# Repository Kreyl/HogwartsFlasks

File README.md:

# HogwartsFlasks
Hogwarts Flasks is a project for realictic models of Hogwarts hourglasses for LARPs and events
You may look at them here https://ostranna.ru/hogwartsflasks (text is at Russian, but photoes are international)

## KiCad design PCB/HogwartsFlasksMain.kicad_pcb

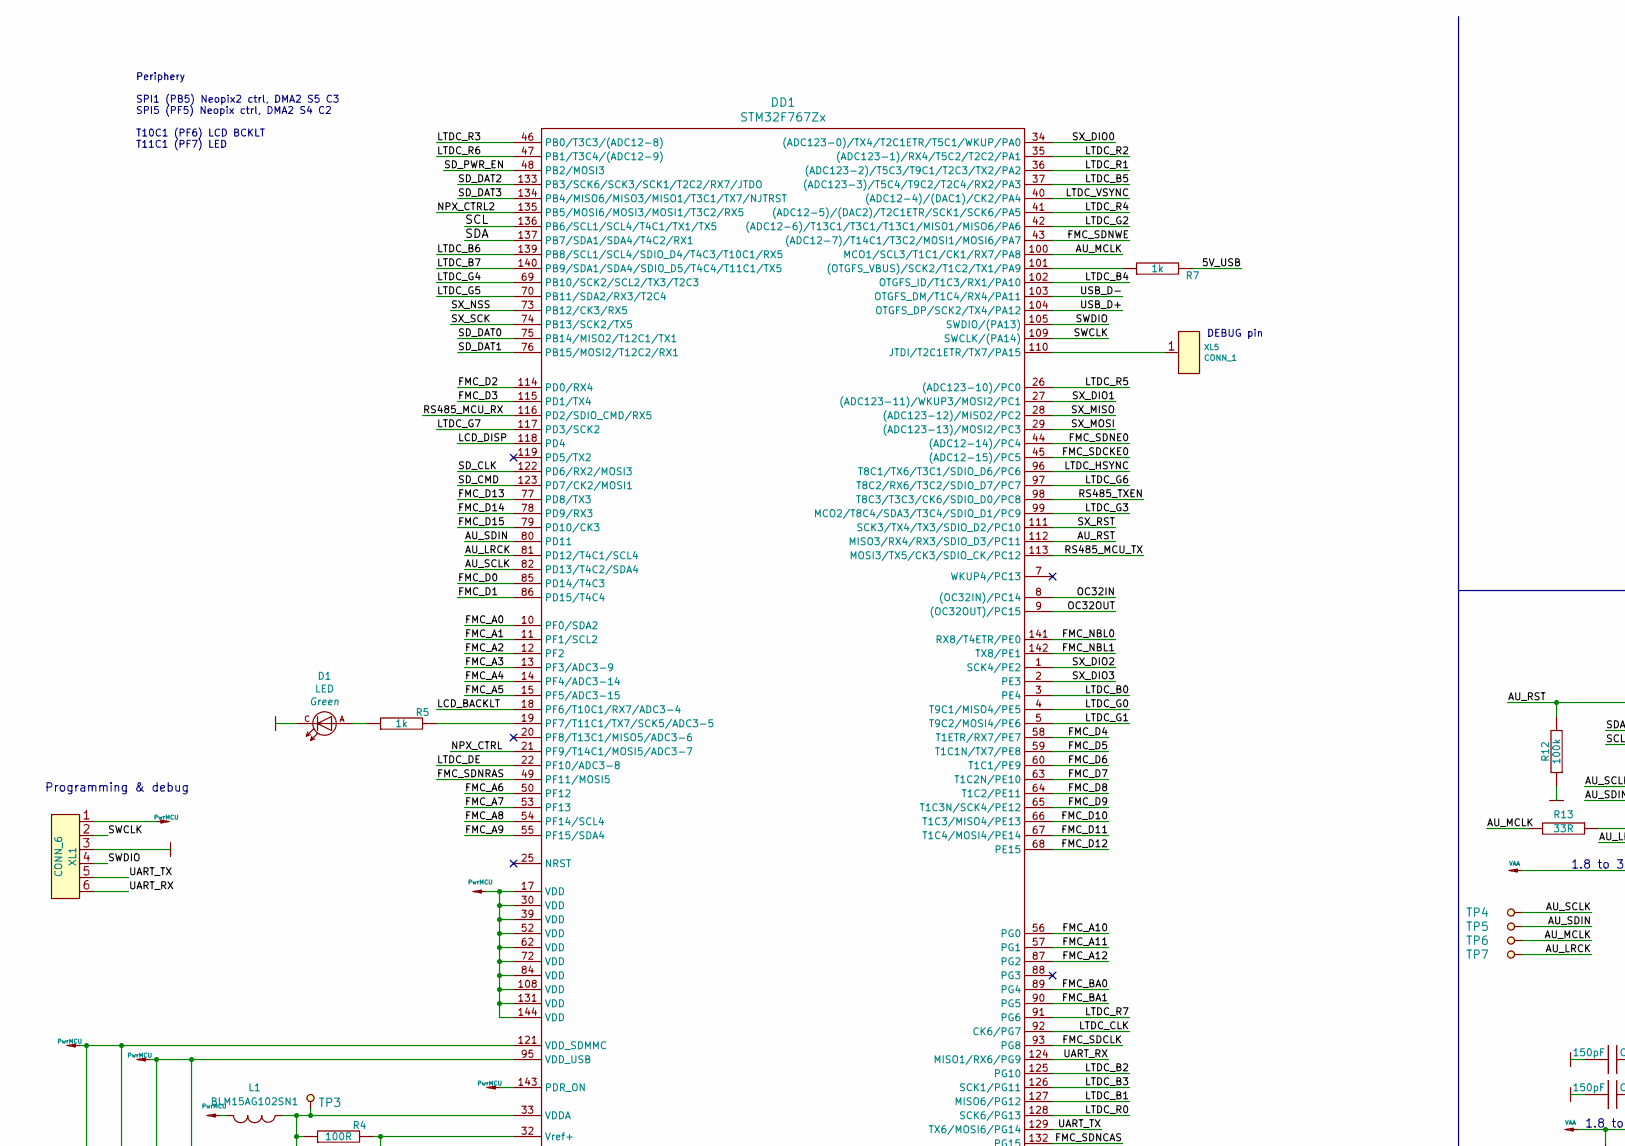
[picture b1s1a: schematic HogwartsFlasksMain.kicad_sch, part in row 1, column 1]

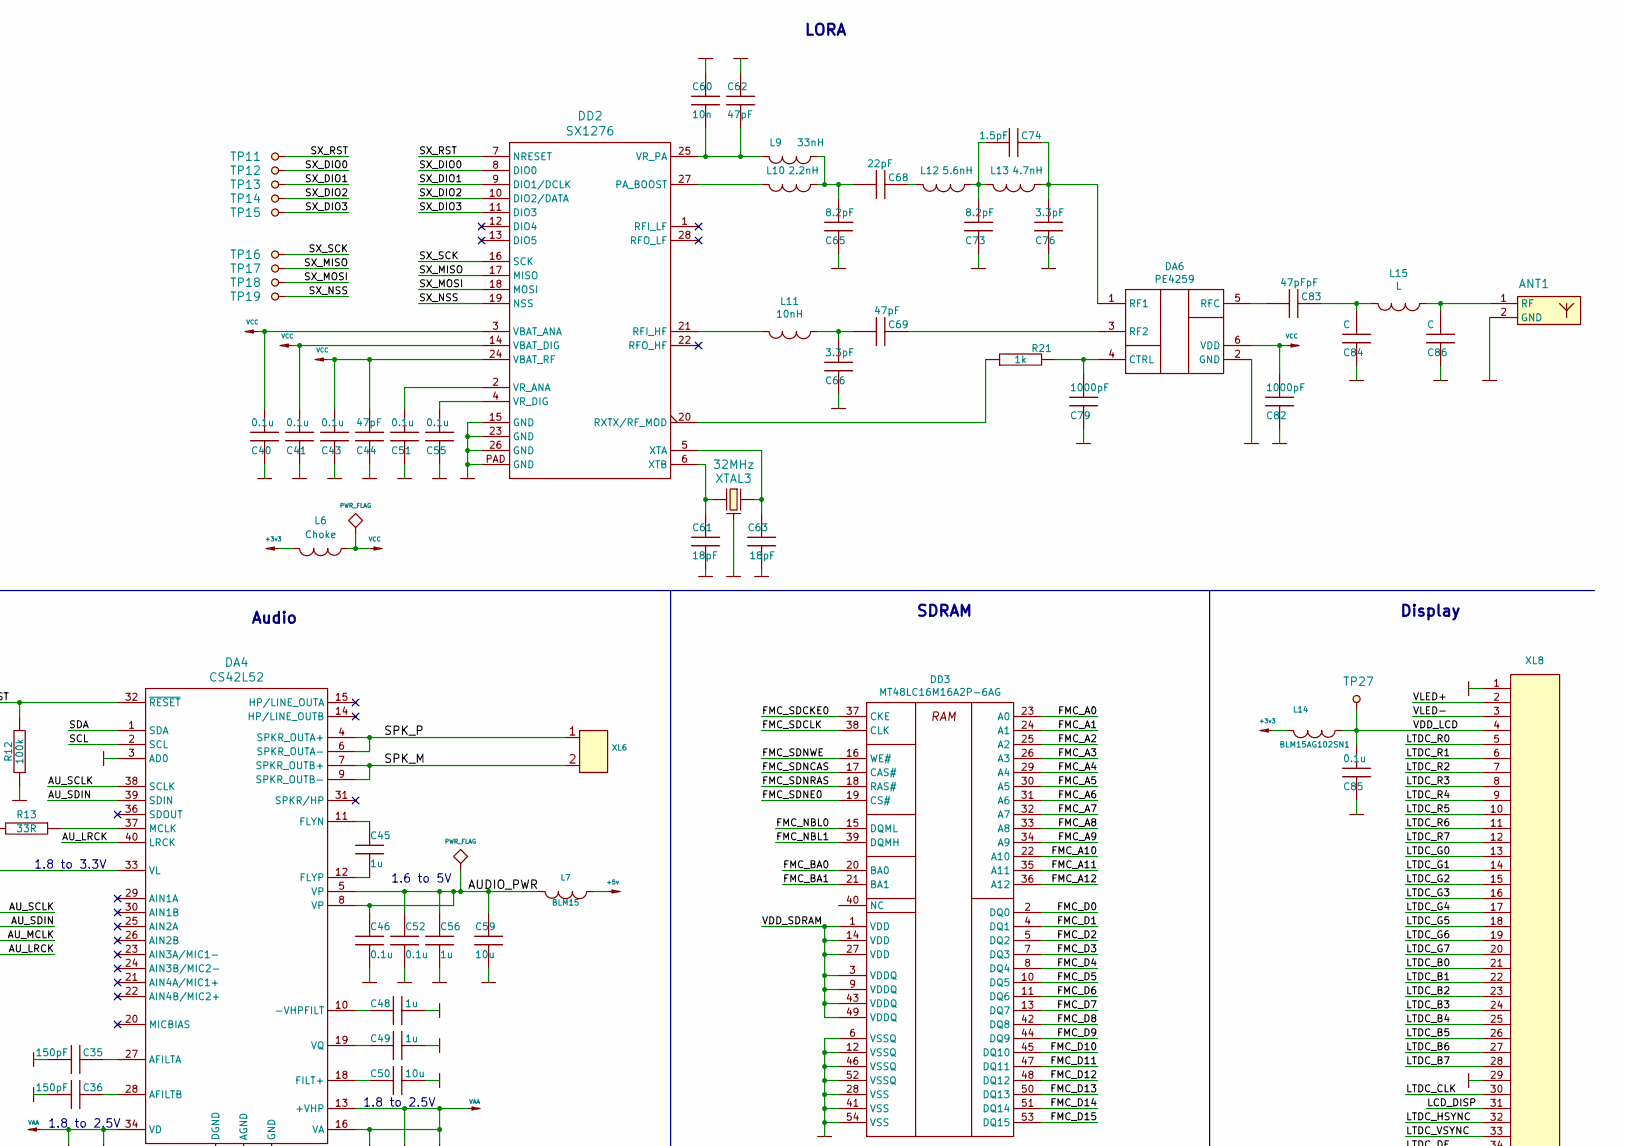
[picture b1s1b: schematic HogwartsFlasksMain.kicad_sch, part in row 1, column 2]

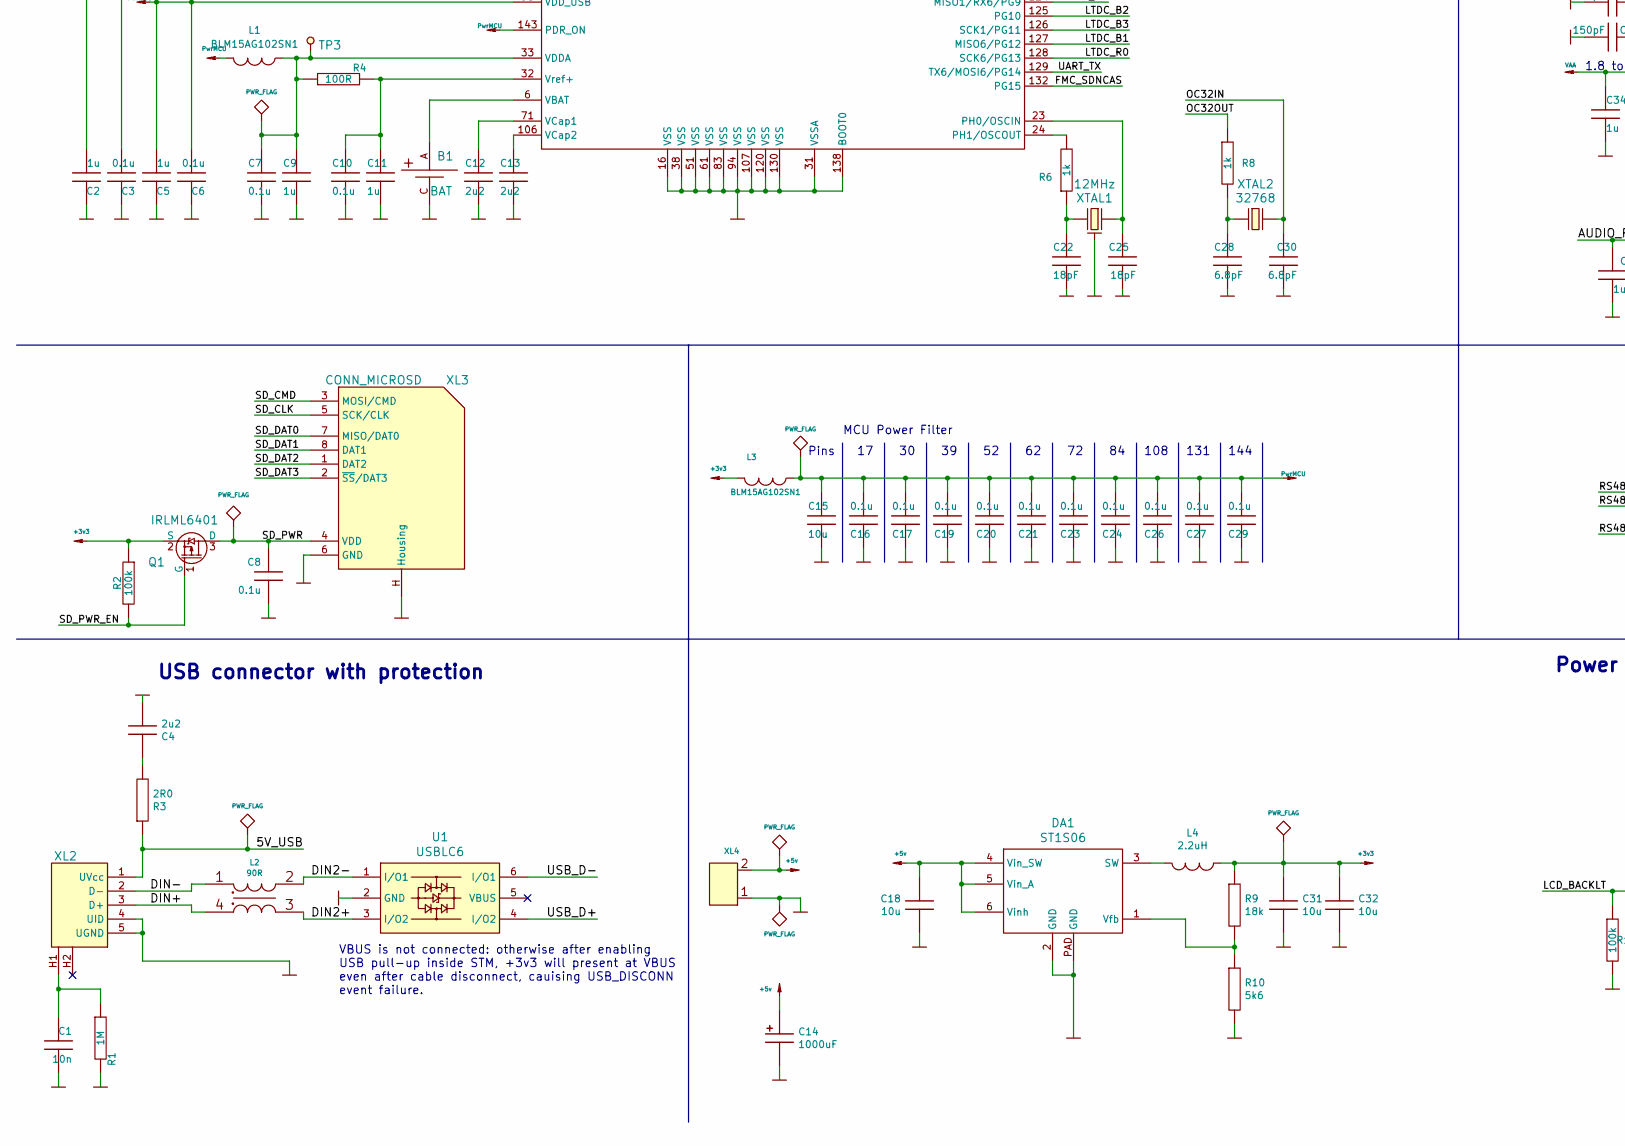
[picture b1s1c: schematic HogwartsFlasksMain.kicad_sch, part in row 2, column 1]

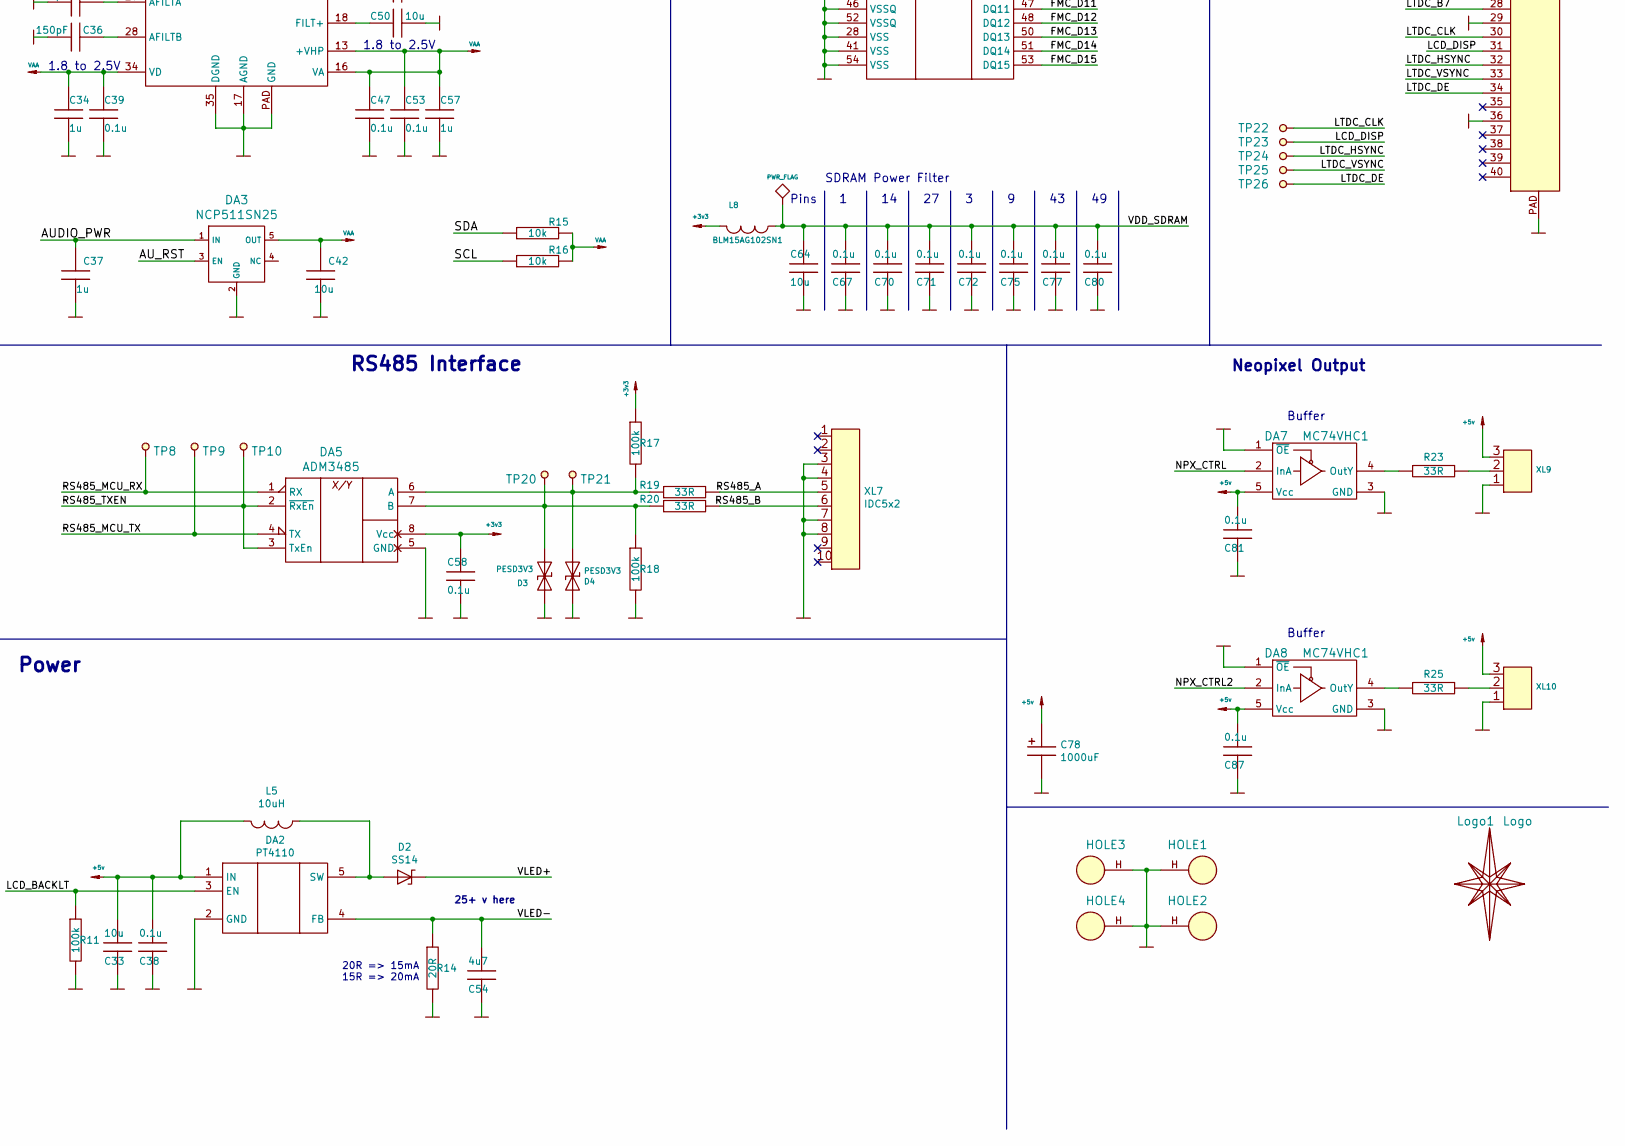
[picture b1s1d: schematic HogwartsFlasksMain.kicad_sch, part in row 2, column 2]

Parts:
ANT1: ANT_GENERAL; ANT_868_IFA_SIMPLEJOY
B1: BAT; BATTERY_CH7410
C1: 10n; CAP_0603_Silks
C2, C5, C9, C11, C34, C37, C45, C48, C49, C56, C57: 1u; CAP_0603_Silks
C3, C6, C7, C8, C10, C16, C17, C19, C20, C21, C23, C24, C26, C27, C29, C38, C39, C46, C47, C52, C53, C58, C67, C70, C71, C72, C75, C77, C80, C81, C85, C87: 0.1u; CAP_0603_Silks
C4, C12, C13: 2u2; CAP_0603_Silks
C14, C78: 1000uF; CAP_10xxR
C15, C18, C31, C32, C33, C42, C50, C59, C64: 10u; CAP_0603_Silks
C22, C25, C61, C63: 18pF; CAP_0603_Silks
C28, C30: 6.8pF; CAP_0603_Silks
C35, C36: 150pF; CAP_0603_Silks
C40, C41, C43, C51, C55: 0.1u; CAP_0402
C44, C62, C69: 47pF; CAP_0402
C54: 4u7; CAP_0805
C60: 10n; CAP_0402
C65, C73: 8.2pF; CAP_0402
C66, C76: 3.3pF; CAP_0402
C68: 22pF; CAP_0402
C74: 1.5pF; CAP_0402
C79, C82: 1000pF; CAP_0402
C83: 47pFpF; CAP_0402
C84, C86: C; CAP_0402
D1: LED; LED_0603
D2: SS14; SMA_DO214AC
D3, D4: PESD3V3; SOD323
DA1: ST1S06; DFN6_3x3
DA2: PT4110; SOT89-5
DA3: NCP511SN25; SOT23-5
DA4: CS42L52; QFN40
DA5: ADM3485; SO8_150MIL
DA6: PE4259; SC70
DA7, DA8: MC74VHC1; SOT23-5
DD1: STM32F767Zx; QFP-144_20x20_Pitch0.5mm
DD2: SX1276; QFN-28_EP_6x6_Pitch0.65mm
DD3: MT48LC16M16A2P-6AG; TSSOP54_400MIL_P08
HOLE1, HOLE2, HOLE3, HOLE4: HOLE_METALLED; Hole3_5_out6mm
L1, L3, L8, L14: BLM15AG102SN1; IND_0402
L2: 90R; DLW21SN
L4: 2.2uH; IND_SRN2512
L5: 10uH; IND_SRN3015
L6: Choke; IND_0402
L7: BLM15; IND_0402
L9: 33nH; IND_0402
L10: 2.2nH; IND_0402
L11: 10nH; IND_0402
L12: 5.6nH; IND_0402
L13: 4.7nH; IND_0402
L15: L; IND_0402
Logo1: Logo; Ostranna_12d7_10d1
Q1: IRLML6401; SOT23-3
R1: 1M; RES_0603
R2, R11, R12, R17, R18: 100k; RES_0603
R3: 2R0; RES_0603
R4: 100R; RES_0603
R5, R6, R7, R8, R21: 1k; RES_0603
R9: 18k; RES_0603
R10: 5k6; RES_0603
R13, R19, R20, R23, R25: 33R; RES_0603
R14: 20R; RES_0603
R15, R16: 10k; RES_0603
TP3, TP4, TP5, TP6, TP7, TP8, TP9, TP10, TP11, TP12, TP13, TP14, TP15, TP16, TP17, TP18, TP19, TP20, TP21, TP22, TP23, TP24, TP25, TP26, TP27: TESTPOINT; TESTPOINT_1MM
U1: USBLC6; SOT23-6
XL1: CONN_6; PLS-6_LOCK
XL2: USB_MICRO_2H; USBmicro_MOLEX_1050170001
XL3: CONN_MICROSD; MICROSD_CAP_FIX05A
XL4: CONN_2; TermiBlockHeader_508_x2_R
XL5: CONN_1; PLS-1Rnd
XL6: CONN_2; W02_Pitch_2d54
XL7: IDC5x2; IDC-Header_2x5_P2.54mm_Vertical
XL8: CONN_40; FFC_0d5x40_flip
XL9, XL10: CONN_3; SLD_3_2D5
XTAL1: 12MHz; 03225C4
XTAL2: 32768; 03215C2
XTAL3: 32MHz; 03225C4

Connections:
+3v3: C31.1, C32.1, C58.2, DA5.8 (Vcc), L3.2, L4.2, L6.2, L8.2, L14.2, Q1.2 (S), R2.1, R9.1, R17.1
+5v: C14.1, C18.1, C33.1, C38.1, C78.1, C81.1, C87.1, DA1.4 (Vin_SW), DA1.5 (Vin_A), DA1.6 (Vinh), DA2.1 (IN), DA7.5 (Vcc), DA8.5 (Vcc), L5.1, L7.2, XL4.2 (PM), XL9.3, XL10.3
/5V_USB: R3.1, R7.2, XL2.1 (UVcc)
/AUDIO_PWR: C37.1, C46.1, C52.1, C56.1, C59.2, DA3.1 (IN), DA4.5 (VP), DA4.8 (VP), L7.1
/AU_LRCK: DA4.40 (LRCK), DD1.81 (PD12/T4C1/SCL4), TP7.1
/AU_MCLK: DD1.100 (MCO1/SCL3/T1C1/CK1/RX7/PA8), R13.2, TP6.1
/AU_RST: DA3.3 (EN), DA4.32 (~RESET), DD1.112 (MISO3/RX4/RX3/SDIO_D3/PC11), R12.2
/AU_SCLK: DA4.38 (SCLK), DD1.82 (PD13/T4C2/SDA4), TP4.1
/AU_SDIN: DA4.39 (SDIN), DD1.80 (PD11), TP5.1
/DIN2+: L2.3, U1.3 (I/O2)
/DIN2-: L2.2, U1.1 (I/O1)
/DIN+: L2.4, XL2.3 (D+)
/DIN-: L2.1, XL2.2 (D-)
/FMC_A0: DD1.10 (PF0/SDA2), DD3.23 (A0)
/FMC_A1: DD1.11 (PF1/SCL2), DD3.24 (A1)
/FMC_A2: DD1.12 (PF2), DD3.25 (A2)
/FMC_A3: DD1.13 (PF3/ADC3-9), DD3.26 (A3)
/FMC_A4: DD1.14 (PF4/ADC3-14), DD3.29 (A4)
/FMC_A5: DD1.15 (PF5/ADC3-15), DD3.30 (A5)
/FMC_A6: DD1.50 (PF12), DD3.31 (A6)
/FMC_A7: DD1.53 (PF13), DD3.32 (A7)
/FMC_A8: DD1.54 (PF14/SCL4), DD3.33 (A8)
/FMC_A9: DD1.55 (PF15/SDA4), DD3.34 (A9)
/FMC_A10: DD1.56 (PG0), DD3.22 (A10)
/FMC_A11: DD1.57 (PG1), DD3.35 (A11)
/FMC_A12: DD1.87 (PG2), DD3.36 (A12)
/FMC_BA0: DD1.89 (PG4), DD3.20 (BA0)
/FMC_BA1: DD1.90 (PG5), DD3.21 (BA1)
/FMC_D0: DD1.85 (PD14/T4C3), DD3.2 (DQ0)
/FMC_D1: DD1.86 (PD15/T4C4), DD3.4 (DQ1)
/FMC_D2: DD1.114 (PD0/RX4), DD3.5 (DQ2)
/FMC_D3: DD1.115 (PD1/TX4), DD3.7 (DQ3)
/FMC_D4: DD1.58 (T1ETR/RX7/PE7), DD3.8 (DQ4)
/FMC_D5: DD1.59 (T1C1N/TX7/PE8), DD3.10 (DQ5)
/FMC_D6: DD1.60 (T1C1/PE9), DD3.11 (DQ6)
/FMC_D7: DD1.63 (T1C2N/PE10), DD3.13 (DQ7)
/FMC_D8: DD1.64 (T1C2/PE11), DD3.42 (DQ8)
/FMC_D9: DD1.65 (T1C3N/SCK4/PE12), DD3.44 (DQ9)
/FMC_D10: DD1.66 (T1C3/MISO4/PE13), DD3.45 (DQ10)
/FMC_D11: DD1.67 (T1C4/MOSI4/PE14), DD3.47 (DQ11)
/FMC_D12: DD1.68 (PE15), DD3.48 (DQ12)
/FMC_D13: DD1.77 (PD8/TX3), DD3.50 (DQ13)
/FMC_D14: DD1.78 (PD9/RX3), DD3.51 (DQ14)
/FMC_D15: DD1.79 (PD10/CK3), DD3.53 (DQ15)
/FMC_NBL0: DD1.141 (RX8/T4ETR/PE0), DD3.15 (DQML)
/FMC_NBL1: DD1.142 (TX8/PE1), DD3.39 (DQMH)
/FMC_SDCKE0: DD1.45 ((ADC12-15)/PC5), DD3.37 (CKE)
/FMC_SDCLK: DD1.93 (PG8), DD3.38 (CLK)
/FMC_SDNCAS: DD1.132 (PG15), DD3.17 (CAS#)
/FMC_SDNE0: DD1.44 ((ADC12-14)/PC4), DD3.19 (CS#)
/FMC_SDNRAS: DD1.49 (PF11/MOSI5), DD3.18 (RAS#)
/FMC_SDNWE: DD1.43 ((ADC12-7)/T14C1/T3C2/MOSI1/MOSI6/PA7), DD3.16 (WE#)
/LCD_BACKLT: DA2.3 (EN), DD1.18 (PF6/T10C1/RX7/ADC3-4), R11.1
/LCD_DISP: DD1.118 (PD4), TP23.1, XL8.31
/LTDC_B0: DD1.3 (PE4), XL8.21
/LTDC_B1: DD1.127 (MISO6/PG12), XL8.22
/LTDC_B2: DD1.125 (PG10), XL8.23
/LTDC_B3: DD1.126 (SCK1/PG11), XL8.24
/LTDC_B4: DD1.102 (OTGFS_ID/T1C3/RX1/PA10), XL8.25
/LTDC_B5: DD1.37 ((ADC123-3)/T5C4/T9C2/T2C4/RX2/PA3), XL8.26
/LTDC_B6: DD1.139 (PB8/SCL1/SCL4/SDIO_D4/T4C3/T10C1/RX5), XL8.27
/LTDC_B7: DD1.140 (PB9/SDA1/SDA4/SDIO_D5/T4C4/T11C1/TX5), XL8.28
/LTDC_CLK: DD1.92 (CK6/PG7), TP22.1, XL8.30
/LTDC_DE: DD1.22 (PF10/ADC3-8), TP26.1, XL8.34
/LTDC_G0: DD1.4 (T9C1/MISO4/PE5), XL8.13
/LTDC_G1: DD1.5 (T9C2/MOSI4/PE6), XL8.14
/LTDC_G2: DD1.42 ((ADC12-6)/T13C1/T3C1/T13C1/MISO1/MISO6/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), XL8.15
/LTDC_G3: DD1.99 (MCO2/T8C4/SDA3/T3C4/SDIO_D1/PC9), XL8.16
/LTDC_G4: DD1.69 (PB10/SCK2/SCL2/TX3/T2C3), XL8.17
/LTDC_G5: DD1.70 (PB11/SDA2/RX3/T2C4), XL8.18
/LTDC_G6: DD1.97 (T8C2/RX6/T3C2/SDIO_D7/PC7), XL8.19
/LTDC_G7: DD1.117 (PD3/SCK2), XL8.20
/LTDC_HSYNC: DD1.96 (T8C1/TX6/T3C1/SDIO_D6/PC6), TP24.1, XL8.32
/LTDC_R0: DD1.128 (SCK6/PG13), XL8.5
/LTDC_R1: DD1.36 ((ADC123-2)/T5C3/T9C1/T2C3/TX2/PA2), XL8.6
/LTDC_R2: DD1.35 ((ADC123-1)/RX4/T5C2/T2C2/PA1), XL8.7
/LTDC_R3: DD1.46 (PB0/T3C3/(ADC12-8)), XL8.8
/LTDC_R4: DD1.41 ((ADC12-5)/(DAC2)/T2C1ETR/SCK1/SCK6/PA5), XL8.9
/LTDC_R5: DD1.26 ((ADC123-10)/PC0), XL8.10
/LTDC_R6: DD1.47 (PB1/T3C4/(ADC12-9)), XL8.11
/LTDC_R7: DD1.91 (PG6), XL8.12
/LTDC_VSYNC: DD1.40 ((ADC12-4)/(DAC1)/CK2/PA4), TP25.1, XL8.33
/NPX_CTRL: DA7.2 (InA), DD1.21 (PF9/T14C1/MOSI5/ADC3-7)
/NPX_CTRL2: DA8.2 (InA), DD1.135 (PB5/MOSI6/MOSI3/MOSI1/T3C2/RX5)
/OC32IN: C30.2, DD1.8 ((OC32IN)/PC14), XTAL2.2
/OC32OUT: DD1.9 ((OC32OUT)/PC15), R8.1
/RS485_A: R19.2, XL7.5
/RS485_B: R20.2, XL7.6
/RS485_MCU_RX: DA5.1 (RX), DD1.116 (PD2/SDIO_CMD/RX5), TP8.1
/RS485_MCU_TX: DA5.4 (TX), DD1.113 (MOSI3/TX5/CK3/SDIO_CK/PC12), TP9.1
/RS485_TXEN: DA5.2 (~RxEn), DA5.3 (TxEn), DD1.98 (T8C3/T3C3/CK6/SDIO_D0/PC8), TP10.1
/SCL: DA4.2 (SCL), DD1.136 (PB6/SCL1/SCL4/T4C1/TX1/TX5), R16.1
/SDA: DA4.1 (SDA), DD1.137 (PB7/SDA1/SDA4/T4C2/RX1), R15.1
/SD_CLK: DD1.122 (PD6/RX2/MOSI3), XL3.5 (SCK/CLK)
/SD_CMD: DD1.123 (PD7/CK2/MOSI1), XL3.3 (MOSI/CMD)
/SD_DAT0: DD1.75 (PB14/MISO2/T12C1/TX1), XL3.7 (MISO/DAT0)
/SD_DAT1: DD1.76 (PB15/MOSI2/T12C2/RX1), XL3.8 (DAT1)
/SD_DAT2: DD1.133 (PB3/SCK6/SCK3/SCK1/T2C2/RX7/JTDO), XL3.1 (DAT2)
/SD_DAT3: DD1.134 (PB4/MISO6/MISO3/MISO1/T3C1/TX7/NJTRST), XL3.2 (~SS~/DAT3)
/SD_PWR: C8.1, Q1.3 (D), XL3.4 (VDD)
/SD_PWR_EN: DD1.48 (PB2/MOSI3), Q1.1 (G), R2.2
/SPK_M: DA4.7 (SPKR_OUTB+), DA4.9 (SPKR_OUTB-), XL6.2 (PM)
/SPK_P: DA4.4 (SPKR_OUTA+), DA4.6 (SPKR_OUTA-), XL6.1
/SWCLK: DD1.109 (SWCLK/(PA14)), XL1.2
/SWDIO: DD1.105 (SWDIO/(PA13)), XL1.4
/SX_DIO0: DD1.34 ((ADC123-0)/TX4/T2C1ETR/T5C1/WKUP/PA0), DD2.8 (DIO0), TP12.1
/SX_DIO1: DD1.27 ((ADC123-11)/WKUP3/MOSI2/PC1), DD2.9 (DIO1/DCLK), TP13.1
/SX_DIO2: DD1.1 (SCK4/PE2), DD2.10 (DIO2/DATA), TP14.1
/SX_DIO3: DD1.2 (PE3), DD2.11 (DIO3), TP15.1
/SX_MISO: DD1.28 ((ADC123-12)/MISO2/PC2), DD2.17 (MISO), TP17.1
/SX_MOSI: DD1.29 ((ADC123-13)/MOSI2/PC3), DD2.18 (MOSI), TP18.1
/SX_NSS: DD1.73 (PB12/CK3/RX5), DD2.19 (NSS), TP19.1
/SX_RST: DD1.111 (SCK3/TX4/TX3/SDIO_D2/PC10), DD2.7 (NRESET), TP11.1
/SX_SCK: DD1.74 (PB13/SCK2/TX5), DD2.16 (SCK), TP16.1
/UART_RX: DD1.124 (MISO1/RX6/PG9), XL1.6
/UART_TX: DD1.129 (TX6/MOSI6/PG14), XL1.5
/USB_D+: DD1.104 (OTGFS_DP/SCK2/TX4/PA12), U1.4 (I/O2)
/USB_D-: DD1.103 (OTGFS_DM/T1C4/RX4/PA11), U1.6 (I/O1)
/VDD_LCD: C85.1, L14.1, TP27.1, XL8.4
/VDD_SDRAM: C64.2, C67.1, C70.1, C71.1, C72.1, C75.1, C77.1, C80.1, DD3.1 (VDD), DD3.3 (VDDQ), DD3.9 (VDDQ), DD3.14 (VDD), DD3.27 (VDD), DD3.43 (VDDQ), DD3.49 (VDDQ), L8.1
/VLED+: D2.C, XL8.2
/VLED-: C54.1, DA2.4 (FB), R14.1, XL8.3
GND: ANT1.2 (GND), B1.C, C1.1, C2.2, C3.2, C4.2, C5.2, C6.2, C7.1, C8.2, C9.1, C10.1, C11.1, C12.1, C13.1, C14.2, C15.1, C16.2, C17.2, C18.2, C19.2, C20.2, C21.2, C22.2, C23.2, C24.2, C25.2, C26.2, C27.2, C28.1, C29.2, C30.1, C31.2, C32.2, C33.2, C34.2, C35.1, C36.1, C37.2, C38.2, C39.2, C40.2, C41.2, C42.2, C43.2, C44.2, C46.2, C47.2, C48.1, C49.1, C50.1, C51.2, C52.2, C53.2, C54.2, C55.2, C56.2, C57.2, C58.1, C59.1, C60.2, C61.2, C62.2, C63.2, C64.1, C65.2, C66.2, C67.2, C70.2, C71.2, C72.2, C73.2, C75.2, C76.2, C77.2, C78.2, C79.2, C80.2, C81.2, C82.2, C84.2, C85.2, C86.2, C87.2, D1.C, D3.A, D4.A, DA1.2 (GND), DA1.PAD (GND), DA2.2 (GND), DA3.2 (GND), DA4.3 (AD0), DA4.17 (AGND), DA4.35 (DGND), DA4.PAD (GND), DA5.5 (GND), DA6.2 (GND), DA7.1 (~OE), DA7.3 (GND), DA8.1 (~OE), DA8.3 (GND), DD1.16 (VSS), DD1.31 (VSSA), DD1.38 (VSS), DD1.51 (VSS), DD1.61 (VSS), DD1.83 (VSS), DD1.94 (VSS), DD1.107 (VSS), DD1.120 (VSS), DD1.130 (VSS), DD1.138 (BOOT0), DD2.15 (GND), DD2.23 (GND), DD2.26 (GND), DD2.PAD (GND), DD3.6 (VSSQ), DD3.12 (VSSQ), DD3.28 (VSS), DD3.41 (VSS), DD3.46 (VSSQ), DD3.52 (VSSQ), DD3.54 (VSS), HOLE1.H, HOLE2.H, HOLE3.H, HOLE4.H, R1.2, R10.2, R11.2, R12.1, R14.2, R18.2, U1.2 (GND), XL1.3, XL2.4 (UID), XL2.5 (UGND), XL3.6 (GND), XL3.H (Housing), XL4.1, XL7.3, XL7.4, XL7.7, XL7.8, XL8.1, XL8.29, XL8.36, XL8.PAD, XL9.1, XL10.1, XTAL1.H, XTAL3.H
unnamed: ANT1.1 (RF), C86.1, L15.2
unnamed: B1.A, DD1.6 (VBAT)
unnamed: C1.2, R1.1, XL2.H1
unnamed: C4.1, R3.2
unnamed: C7.2, C9.2, DD1.33 (VDDA), L1.1, R4.1, TP3.1
unnamed: C10.2, C11.2, DD1.32 (Vref+), R4.2
unnamed: C12.2, DD1.71 (VCap1)
unnamed: C13.2, DD1.106 (VCap2)
unnamed: C22.1, R6.1, XTAL1.2
unnamed: C25.1, DD1.23 (PH0/OSCIN), XTAL1.1
unnamed: C28.2, R8.2, XTAL2.1
unnamed: C35.2, DA4.27 (AFILTA)
unnamed: C36.2, DA4.28 (AFILTB)
unnamed: C45.1, DA4.11 (FLYN)
unnamed: C45.2, DA4.12 (FLYP)
unnamed: C48.2, DA4.10 (-VHPFILT)
unnamed: C49.2, DA4.19 (VQ)
unnamed: C50.2, DA4.18 (FILT+)
unnamed: C51.1, DD2.2 (VR_ANA)
unnamed: C55.1, DD2.4 (VR_DIG)
unnamed: C60.1, C62.1, DD2.25 (VR_PA), L9.1
unnamed: C61.1, DD2.6 (XTB), XTAL3.2
unnamed: C63.1, DD2.5 (XTA), XTAL3.1
unnamed: C65.1, C68.2, L9.2, L10.2
unnamed: C66.1, C69.2, L11.2
unnamed: C68.1, L12.1
unnamed: C69.1, DA6.3 (RF2)
unnamed: C73.1, C74.2, L12.2, L13.1
unnamed: C74.1, C76.1, DA6.1 (RF1), L13.2
unnamed: C79.1, DA6.4 (CTRL), R21.2
unnamed: C83.1, C84.1, L15.1
unnamed: C83.2, DA6.5 (RFC)
unnamed: D1.A, R5.1
unnamed: D2.A, DA2.5 (SW), L5.2
unnamed: D3.C, DA5.7 (B), R18.1, R20.1, TP20.1
unnamed: D4.C, DA5.6 (A), R17.2, R19.1, TP21.1
unnamed: DA1.1 (Vfb), R9.2, R10.1
unnamed: DA1.3 (SW), L4.1
unnamed: DA4.37 (MCLK), R13.1
unnamed: DA7.4 (OutY), R23.2
unnamed: DA8.4 (OutY), R25.2
unnamed: DD1.19 (PF7/T11C1/TX7/SCK5/ADC3-5), R5.2
unnamed: DD1.24 (PH1/OSCOUT), R6.2
unnamed: DD1.101 ((OTGFS_VBUS)/SCK2/T1C2/TX1/PA9), R7.1
unnamed: DD1.110 (JTDI/T2C1ETR/TX7/PA15), XL5.1
unnamed: DD2.20 (RXTX/RF_MOD), R21.1
unnamed: DD2.21 (RFI_HF), L11.1
unnamed: DD2.27 (PA_BOOST), L10.1
unnamed: R23.1, XL9.2 (PM)
unnamed: R25.1, XL10.2 (PM)
PwrMCU: C2.1, C3.1, C5.1, C6.1, C15.2, C16.1, C17.1, C19.1, C20.1, C21.1, C23.1, C24.1, C26.1, C27.1, C29.1, DD1.17 (VDD), DD1.30 (VDD), DD1.39 (VDD), DD1.52 (VDD), DD1.62 (VDD), DD1.72 (VDD), DD1.84 (VDD), DD1.95 (VDD_USB), DD1.108 (VDD), DD1.121 (VDD_SDMMC), DD1.131 (VDD), DD1.143 (PDR_ON), DD1.144 (VDD), L1.2, L3.1, XL1.1
VAA: C34.1, C39.1, C42.1, C47.1, C53.1, C57.1, DA3.5 (OUT), DA4.13 (+VHP), DA4.16 (VA), DA4.33 (VL), DA4.34 (VD), R15.2, R16.2
VCC: C40.1, C41.1, C43.1, C44.1, C82.1, DA6.6 (VDD), DD2.3 (VBAT_ANA), DD2.14 (VBAT_DIG), DD2.24 (VBAT_RF), L6.1

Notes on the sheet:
Programming & debug
Periphery SPI1 (PB5) Neopix2 ctrl, DMA2 S5 C3 SPI5 (PF5) Neopix ctrl, DMA2 S4 C2 T10C1 (PF6) LCD BCKLT T11C1 (PF7) LED
USB connector with protection
VBUS is not connected: otherwise after enabling USB pull-up inside STM, +3v3 will present at VBUS even after cable disconnect, cauising USB_DISCONN event failure.
Pins
MCU Power Filter
108
131
DEBUG pin
144
1.8 to 3.3V
1.8 to 2.5V
Power
Audio
20R => 15mA 15R => 20mA
1.6 to 5V
25+ v here
RS485 Interface
LORA
SDRAM Power Filter
SDRAM
Neopixel Output
Buffer
Display

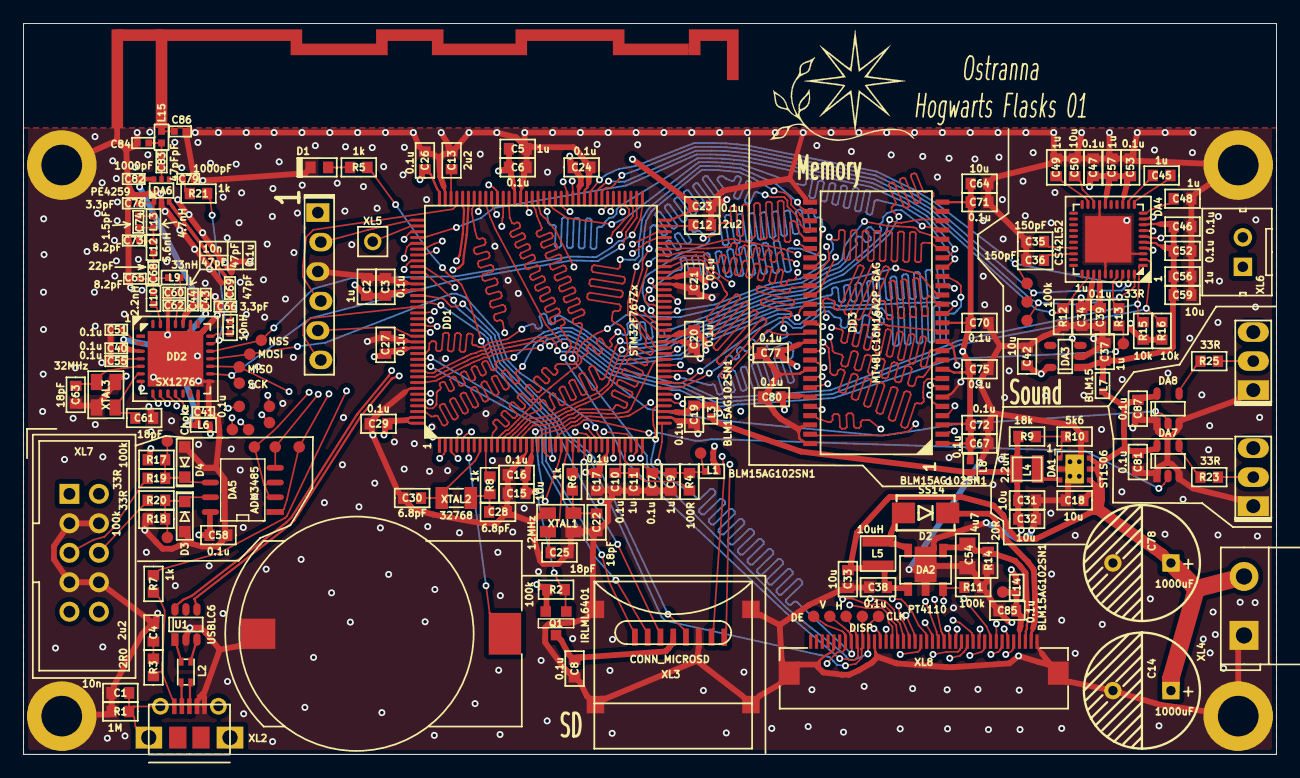
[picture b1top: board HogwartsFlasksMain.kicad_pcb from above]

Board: 4 copper layers, 108.0 x 63.0 mm, 187 parts (0 on the bottom side), 176 nets.

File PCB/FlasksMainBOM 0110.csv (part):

Reference,Type,Quantity,Value,Footprint,Price,Sum,SP,SPDip,SP Total,PN,URL,Description,,,,,
"ANT1,",,1,ANT_GENERAL,Antennas:ANT_868_IFA_SIMPLEJOY,0,0,0,0,0,-,-,-,do not mount,,,,
"B1,",,1,BAT,Installation:BATTERY_CH7410,35,35,2,0,2,-,http://www.quartz1.com/price/model.php?group=2684&mark=CH7410-2032,,,,,,
"C1,",Capacitor,1,10n,Capacitors:CAP_0603,"0,29","0,29",2,0,2,CC0603KRX7R7BB103,https://www.terraelectronica.ru/product/595783,,"Any Capacitor 10n case 0603, x5r or x7r or np0 isolator",,,,
"C5, C11, C9, C2, C34, C57, C48, C49, C45, C37, C56,",Capacitor,11,1u,Capacitors:CAP_0603,"0,37","4,07",2,0,22,CL10A105KP8NNNC,https://www.terraelectronica.ru/product/882689,,"Any Capacitor 1u case 0603, x5r or x7r or np0 isolator",,,,
"C13, C12, C4,",Capacitor,3,2u2,Capacitors:CAP_0603,"0,62","1,86",2,0,6,CL10A225KQ8NNNC,https://www.terraelectronica.ru/product/863292,,"Any Capacitor 2u2 case 0603, x5r or x7r or np0 isolator",,,,
"C15, C64, C50, C42, C59, C18, C31, C32, C33,",Capacitor,9,10u,Capacitors:CAP_0603,"0,61","5,49",2,0,18,GRM188R60G106ME47D,https://www.terraelectronica.ru/product/367594,,"Any Capacitor 10u case 0603, x5r or x7r or np0 isolator",,,,
"C16, C17, C19, C20, C21, C23, C24, C26, C27, C29, C6, C10, C7, C3, C77, C75, C70, C71, C67, C72, C80, C85, C81, C39, C53, C47, C46, C52, C8, C58, C38, C87,",Capacitor,32,0.1u,Capacitors:CAP_0603,"0,24","7,68",2,0,64,CL10B104KB8NNND,https://www.terraelectronica.ru/product/863315,,"Any Capacitor 0.1u case 0603, x5r or x7r or np0 isolator",,,,
"C22, C25, C61, C63,",Capacitor,4,18pF,Capacitors:CAP_0603,"0,23","0,92",2,0,8,CC0603JRNPO9BN180,https://www.terraelectronica.ru/product/326939,,"Any Capacitor 18pF case 0603, x5r or x7r or np0 isolator",,,,
"C28, C30,",Capacitor,2,6.8pF,Capacitors:CAP_0603,"0,45","0,9",2,0,4,CL10C6R8CB8NNNC,https://www.terraelectronica.ru/product/863469,,"Any Capacitor 6.8pF case 0603, x5r or x7r or np0 isolator",,,,
"C36, C35,",Capacitor,2,150pF,Capacitors:CAP_0603,"0,5",1,2,0,4,CL10C151JB8NNNC,https://www.terraelectronica.ru/product/863401,,"Any Capacitor 150pF case 0603, x5r or x7r or np0 isolator",,,,
"C44, C62, C69, С83",Capacitor,3,47pF,Capacitors:CAP_0402 100 шт,"0,22","0,66",2,0,6,CC0402JRNPO9BN470,https://www.terraelectronica.ru/product/567824,,"Any Capacitor 47pF case 0402, x5r or x7r or np0 isolator",,,,
"C51, C41, C40, C43, C55,",Capacitor,5,0.1u,Capacitors:CAP_0402,"0,16","0,8",2,0,10,CL05A104KA5NNNC,https://www.terraelectronica.ru/product/863209,,"Any Capacitor 0.1u case 0402, x5r or x7r or np0 isolator",,,,
"C54,",Capacitor,1,4u7,Capacitors:CAP_0805,"1,1","1,1",2,0,2,GRM21BR61E475KA12L,https://www.terraelectronica.ru/product/343068,,"Any Capacitor 4u7 case 0805, x5r or x7r or np0 isolator, 25V",,,,куплено 10 шт
"C60,",Capacitor,1,10n,Capacitors:CAP_0402,"0,17","0,17",2,0,2,CL05B103JB5NNNC,https://www.terraelectronica.ru/product/575020,,"Any Capacitor 10n case 0402, x5r or x7r or np0 isolator",,,,
"C65, C73,",Capacitor,2,8.2pF,Capacitors:CAP_0402 100 шт,"0,24","0,48",2,0,4,CC0402DRNPO9BN8R2,https://www.terraelectronica.ru/product/1136580,,"Any Capacitor 8.2pF case 0402, x5r or x7r or np0 isolator",,,,куплено 100 шт
"C66, C76,",Capacitor,2,3.3pF,Capacitors:CAP_0402,"0,24","0,48",2,0,4,CC0402CRNPO9BN3R6,https://www.terraelectronica.ru/product/866766,,"Any Capacitor 3.3pF case 0402, x5r or x7r or np0 isolator",,,,
"C68,",Capacitor,1,22pF,Capacitors:CAP_0402 100 шт,"0,21","0,21",2,0,2,GRM1555C1H220FA01D,https://www.terraelectronica.ru/product/866760,,"Any Capacitor 22pF case 0402, x5r or x7r or np0 isolator",,,,
"C74,",Capacitor,1,1.5pF,Capacitors:CAP_0402,"0,16","0,16",2,0,2,GRM1555C1H1R5CA01D,https://www.terraelectronica.ru/product/866759,,"Any Capacitor 1.5pF case 0402, x5r or x7r or np0 isolator",,,,
"C78, C14,",,2,1000uF,Capacitors:CAP_10xxR диаметр 10 мм,"14,5",29,2,0,4,CA006M1000REG-1010,https://www.terraelectronica.ru/product/624735,,,,,,
"C82, C79,",Capacitor,2,1000pF,Capacitors:CAP_0402,"0,12","0,24",2,0,4,CC0402KRX7R7BB102,https://www.terraelectronica.ru/product/337970,,"Any Capacitor 1000pF case 0402, x5r or x7r or np0 isolator",,,,
"C86, C84,",,2,C,Capacitors:CAP_0402,,0,,,0,,,,,,,,
"D1,",,1,LED,LEDs:LED_0603,5,5,6,0,6,-,-,,,,,,
"D2,",,1,SS14,Diodes:SMA_DO214AC,2,2,2,0,2,SS14,https://www.terraelectronica.ru/product/1006032,,,,,,
и,PN,2,PESD3V3,Diodes:SOD323,"4,1","8,2",2,0,4,PESD3V3,https://www.terraelectronica.ru/product/247487,,,,,,
"DA1,",PN,1,ST1S06,QFN_DFN:DFN6_3x3,"56,5","56,5",6,0,6,ST1S06,https://www.terraelectronica.ru/product/298082,,купили 5,,,,
"DA2,",PN,1,PT4110,SOT:SOT89-5,13,13,6,0,6,PT4110,"https://ru.aliexpress.com/item/32909145567.html?spm=a2g0o.pr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,searchweb201602_2,searchweb201603_53",,,,,,
"DA3,",PN,1,NCP511SN25,SOT:SOT23-5,"23,1","23,1",5,0,5,NCP511SN25,https://www.terraelectronica.ru/product/361863,https://onelec.ru/products/ncp511sn25 0,,,,,
"DA4,",PN,1,CS42L52,QFN_DFN:QFN40,75,75,40,0,40,CS42L52,https://ru.aliexpress.com/item/32793385956.html?spm=a2g0s.90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,,,,,,
"DA5,",PN,1,ADM3485,SO_DIL_TSSOP:SO8_150MIL,"49,3",160,8,0,8,ADM3485EARZ,https://www.terraelectronica.ru/product/25424,,,,,,
"DA6,",PN,1,PE4259,SOT:SC70,31,31,6,0,6,PE4259,https://www.terraelectronica.ru/product/1267775,,,,,,
"DA7, DA8",PN,2,MC74VHC1,SOT:SOT23-5,"2,5","3,6",5,0,5,MC74VHC1G14DFT1G,https://www.terraelectronica.ru/product/435342,,,,,,
"DD1,",PN,1,STM32F767Z,LQFP_TQFP:QFP-144_20x20_Pitch0.5mm 5,1490,1490,144,0,144,,https://www.terraelectronica.ru/product/2120933,,купили 5,,,,
"DD2,",PN,1,SX1276,QFN_DFN:QFN-28_EP_6x6_Pitch0.65mm,328,328,28,0,28,SX1276IMLTRT,https://www.terraelectronica.ru/product/1289335,,,,,,
"DD3,",PN,1,MT48LC16M16A2P-6AG,SO_DIL_TSSOP:TSSOP54_400MIL_P08,277,277,54,0,54,MT48LC16M16A2P-6AG,https://www.terraelectronica.ru/product/1200409,,купили 5,,,,
"HOLE1, HOLE2, HOLE3, HOLE4,",,4,HOLE_METALLED,PCB:Hole3_5_out6mm,,0,,,0,,,,,,,,
"L2,",,1,90R,Inductors:DLW21SN,"7,6","7,6",2,0,2,DLW21SN900SQ2,https://www.terraelectronica.ru/product/333735,,покупали ранее?,,,,
"L3, L1, L8, L14, L7",PN,4,BLM15AG102SN1,Inductors:IND_0402,"0,43","1,72",2,0,8,BLM15AG102SN1,https://www.terraelectronica.ru/product/225140,,,,,,
"L4,",Inductor,1,2.2uH,Inductors:IND_SRN2512,"10,3","10,3",2,0,2,SRN2512-2R2M,https://www.terraelectronica.ru/search?text=SRN2512-2R2M,,Any Inductor 2.2uH case SRN2512,,,,
"L5,",Inductor,1,10uH,Inductors:IND_SRN3015,"3,3","3,3","15,4",2,"17,4",SRN3015-100M,https://www.terraelectronica.ru/product/1638207,,Any Inductor 10uH case SRN3015,,,,
"L6,",,1,SBY100505T-102Y-N,Inductors:IND_0402,"0,16","0,16",2,0,2,SBY100505T-102Y-N,https://www.terraelectronica.ru/product/1922419,,,,,,
"L9,",Inductor,1,33nH,Inductors:IND_0402,1,1,2,0,2,LQG15HN33NJ02D,https://www.terraelectronica.ru/product/339131,,Any Inductor 33nH case 0402,,,,
"L10,",Inductor,1,2.2nH,Inductors:IND_0402,"1,2","1,2",2,0,2,LQG15HN2N2S02D,https://www.terraelectronica.ru/product/329804,,Any Inductor 2.2nH case 0402,,,,
"L11,",Inductor,1,10nH,Inductors:IND_0402,"0,96","0,96",2,0,2,LQG15HN10NJ02D,https://www.terraelectronica.ru/product/1025644,,Any Inductor 10nH case 0402,,,,
"L12,",Inductor,1,5.6nH,Inductors:IND_0402,"0,52","0,52",2,0,2,LQG15HS5N6S02D,https://www.terraelectronica.ru/product/867408,,Any Inductor 5.6nH case 0402,,,,
"L13,",Inductor,1,4.7nH,Inductors:IND_0402,"0,32","0,32",2,0,2,LQG15HS4N7S02D,https://www.terraelectronica.ru/product/1025621,,Any Inductor 4.7nH case 0402,,,,
"L15,",,1,L,Inductors:IND_0402,,0,,,0,,,,,,,,
"Logo1,",,1,Logo,Pictures:Ostranna_16d9_13d5,,0,,,0,,,,,,,,
"Q1,",PN,1,IRLML6401,SOT:SOT23-3,"5,6","5,6",3,0,3,IRLML6401,https://www.terraelectronica.ru/product/180111,,,,,,
"R1,",Resistor,1,1M,Resistors:RES_0603,"0,14","0,14",2,0,2,RC0603FR-071ML,https://www.terraelectronica.ru/product/441621,,Any Resistor 1M case 0603 1%,,,,
"R3,",Resistor,1,2R0,Resistors:RES_0603,"0,17","0,17",2,0,2,RC0603FR-072RL,https://www.terraelectronica.ru/product/679314,,Any Resistor 2R0 case 0603 1%,,,,
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
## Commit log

2019-08-31 + Sch seems done
2019-09-04 PCB Layout done
2019-09-23 PCB tracing started
2019-09-28 Proceeding with tracing
2019-09-29 PCB sent to factory
2019-09-29 minor
2019-10-09 BOM added
2019-10-10 + OS asm started
2019-10-13 UART works ok
2019-10-13 + SetCoreClock 80 MHz works ok
2019-10-13 + LED works
2019-10-13 + WS2812 block seems working
2019-10-13 + SD works
2019-10-13 + Backup register storage works ok
2019-10-15 + Lume + Points Still not tested
2019-10-15 + Lume works + Points work
2019-11-03 MainPCB: Usb does not work somehow
2019-11-04 + FlasksScreen project + SDRAM works
2019-11-04 Sdram init clean-up
2019-11-20 Working on LTDC
2019-11-21 + LCD works at first. Two rectangles drawn.
2019-11-21 * Framebuf1 successfully moved to SDRAM
2019-11-22 * Fix display clk * Display code clean-up + ColorARGB_t
2019-11-24 + PNG decoder
2019-11-24 - PNG
2019-11-24 * Some bitmap decoder clean-up
2019-11-24 + Uncompressed paletted8 BMP works
2019-11-24 * ColorTable and Line moved to static arrays to increase speed
2019-12-26 Something
2020-04-18 * Switch to Stm32CubeIDE
2020-04-18 + Switch succeded + SDRAM works
2020-04-25 Working on LoRa
2020-04-26 * Flasks and Lume work
2020-08-08 switch to 216 MHz SDRAM settings appended
2020-08-08 Fighting w screen
2020-08-08 Display works
2020-08-11 + Fighting with JPEG
2020-08-11 Fighting w JPEG
2020-08-13 Video is playing!
2020-08-15 Something cracked
2020-08-15 Fixed
2020-08-15 Clean-up in progress
2020-08-15 Same
2020-08-16 Reading audiochunk is slow due to seek operation
2020-08-17 + FLASH ART
2020-08-17 - DMA2D
2020-08-17 Successfully switched to RGB888
2020-08-18 DMA changed, video keeps working
2020-08-18 Some reorganisation in preparation to read audio
2020-08-18 Proceeding
2020-08-18 Double buffer for both video and audio, reading same way. Slow.
2020-08-19 Experiments w cache
2020-08-19 Before switching to simpler buffer
2020-08-19 Some trash
2020-08-19 Seems like working buffer
2020-08-20 Audio plays using big buffer. Cache issues lead to clicks.
2020-08-20 + Audio chunk read. Way too slow.
2020-08-20 Seems working smoothly
2020-08-21 Before sync
2020-08-21 Sync by audio chunks failed idea due to diverse chunks sequence
2020-08-21 + Frame timing adjusted to sync with sound
2020-08-21 Clean-up of Dbg messages
2020-08-26 Buttons Started
2020-08-26 Code seems working
2020-08-26 + Switch between 27 & 216MHz
2020-08-26 + Init/deinit seems ok
2020-08-27 + Wav plays
2020-08-27 Working somehow
2020-08-31 Release
2020-10-30 + v2: LCD connector fixed
2020-11-13 Something minor
2021-01-09 Smth merged
2021-01-19 Lora started
2021-04-10 * Switch to newer KiCAD
2021-04-10 * Screen code added, not working now
2021-05-04 Before switching to LS codec code
2021-05-04 Everything works, Flasks are back
2021-05-05 Points add-remove seems good
2021-05-05 Sound works ok
2021-05-10 + Volume setup + Volume saved to bckp reg
2021-05-16 Working with Lora. TX written, but does not work.
2021-05-29 Max value increments/decrements by 500.
2021-10-18 Lora works
2021-10-19 Lora RC
2021-11-04 + font + Control SW
2022-01-30 Works again
2024-04-19 Move to eclipse Refactoring
2024-04-19 SetNow works
2024-04-19 Hide and show work
2024-04-19 Trying to switch screen to eclipse. Does not work
2024-04-19 Still no success
2024-04-19 Flasks screen works + png2h.py tool works ok
2024-04-20 + ellipsis + png 2 h + screen hide cmd
2024-04-20 Refactoring
2024-04-20 Adding radio control
2024-04-20 Setting now controls visibility, too
2024-04-20 + Time control by radio
2024-04-20 Switch from "hidden" to "shown" logic
2024-05-25 Reply made same for radio and shell
